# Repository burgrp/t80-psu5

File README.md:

# T80-PSU5
Power supply with 5V input and 3.3V 0.8A LDO regulator.

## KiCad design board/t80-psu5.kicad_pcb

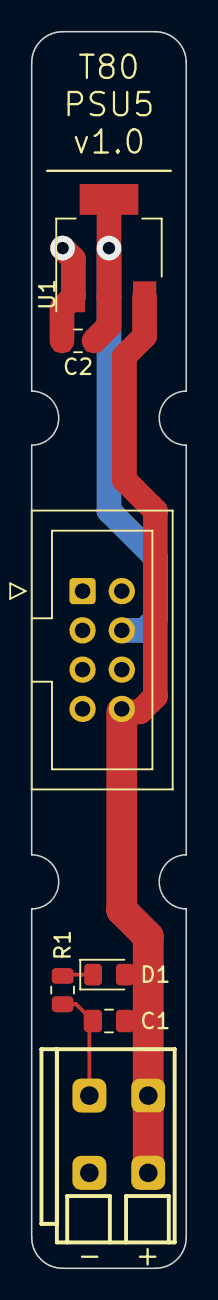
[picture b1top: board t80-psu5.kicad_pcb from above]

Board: 2 copper layers, 10.0 x 80.0 mm, 7 parts (0 on the bottom side), 4 nets.

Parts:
C1, C2: 10u; C_0805_2012Metric_Pad1.18x1.45mm_HandSolder
D1: WHITE; LED_0805_2012Metric_Pad1.15x1.40mm_HandSolder
J1: Conn_01x02_Female; DG235-3.81-02P
R1: 1k5; R_0805_2012Metric
U1: LM1117-3.3; SOT-223-3_TabPin2
X3: IDC-Header_2x04_P2.54mm_Vertical

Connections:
+3V3: C2.1, U1.2 (VO), X3.4 (3V3)
+5V: C1.1, D1.2 (A), J1.2, U1.3 (VI), X3.8 (5V)
GND: C1.2, C2.2, J1.1, R1.2, U1.1 (GND), X3.1 (GND), X3.7 (GND)
unnamed: D1.1 (K), R1.1

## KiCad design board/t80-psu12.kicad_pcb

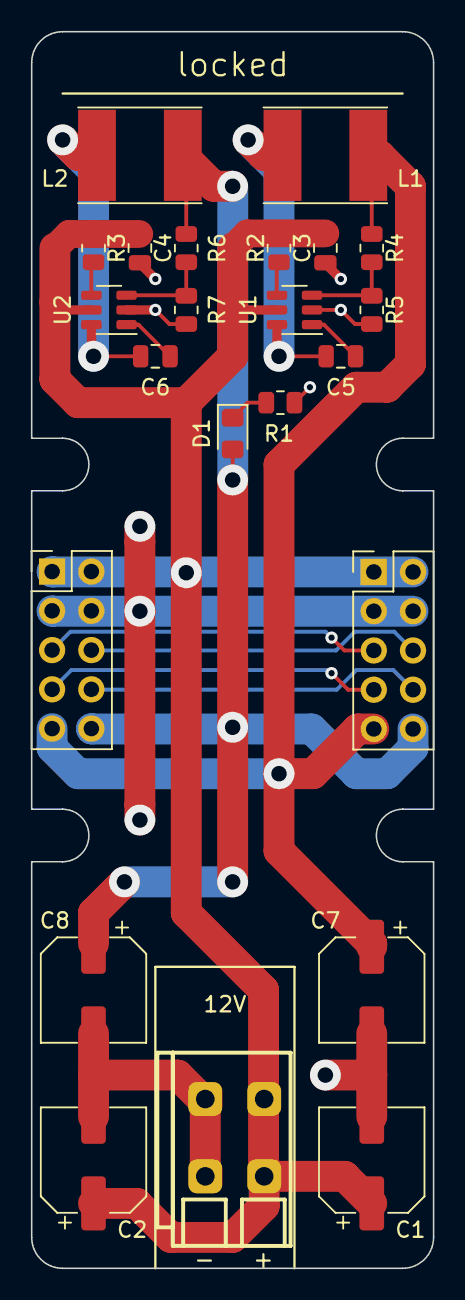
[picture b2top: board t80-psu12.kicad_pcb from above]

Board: 2 copper layers, 26.0 x 80.0 mm, 28 parts (0 on the bottom side), 21 nets.

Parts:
C1, C2, C7, C8: 100u/12V; CP_Elec_6.3x5.4
C3, C4, C5, C6: 100n; C_0805_2012Metric
D1: WHITE; LED_0805_2012Metric_Pad1.15x1.40mm_HandSolder
J1: Conn_01x02_Female; DG235-3.81-02P
L1, L2: 6.8uH; CKCS6028
NT1, NT2, NT3, NT4, NT5: NetTie_2; NetTie-2mm-T80
R1: 1k5; R_0805_2012Metric
R2, R3: 100k; R_0805_2012Metric
R4: 30.9k 1%; R_0805_2012Metric
R5: 4.22k 1%; R_0805_2012Metric
R6: 30k 1%; R_0805_2012Metric
R7: 6.65k 1%; R_0805_2012Metric
U1, U2: FR8205; SOT-23-6
X1, X2: PinHeader_2x05_P2.54mm_Vertical

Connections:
+3V3: C8.1, D1.2 (A), L2.2, NT3.2, R6.2
+5V: C7.1, L1.2, NT2.2, R4.2
+12V: C1.1, C2.1, C3.2, C4.2, J1.2, NT1.2, R2.2, R3.2, U1.5 (VIN), U2.5 (VIN)
/IRQ: X1.8 (IRQ), X2.8 (IRQ)
/PWR_LINE_3V3: NT3.1, X1.10 (3V3), X2.10 (3V3)
/PWR_LINE_5V: NT2.1, X1.9 (5V), X2.9 (5V)
/PWR_LINE_12V: NT1.1, X1.1 (12V), X1.2 (12V), X2.1 (12V), X2.2 (12V)
/PWR_LINE_GND: NT4.1, NT5.1, X1.3 (GND), X1.4 (GND), X2.3 (GND), X2.4 (GND)
/RST: X1.7 (RST), X2.7 (RST)
/SCL: X1.5 (SCL), X2.5 (SCL)
/SDA: X1.6 (SDA), X2.6 (SDA)
GND: C1.2, C2.2, C3.1, C4.1, C7.2, C8.2, J1.1, NT4.2, NT5.2, R1.2, R5.1, R7.1, U1.2 (GND), U2.2 (GND)
unnamed: D1.1 (K), R1.1
unnamed: C5.1, U1.1 (BST)
unnamed: R4.1, R5.2, U1.3 (FB)
unnamed: C5.2, L1.1, U1.6 (LX)
unnamed: R2.1, U1.4 (SHDN)
unnamed: C6.1, U2.1 (BST)
unnamed: R6.1, R7.2, U2.3 (FB)
unnamed: C6.2, L2.1, U2.6 (LX)
unnamed: R3.1, U2.4 (SHDN)
